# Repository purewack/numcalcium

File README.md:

# NumCalcium

NumCalcium is a calculator-like USB + Bluetooth Numpad keyboard. This is the primary intended function, however, because it is powered by MicroPython, users are able to write their own programs for it.
There were a number of different hardware and software revision before I settled on a combination of an ESP32 S3 and MicroPython. It made so much sense for the applications that I wanted to achieve, and was far easier to get working than my previous attempts with STM32F103 and a custom system in C, more about the development history below if you're interested :)

## Installation

You can download the release binary and flash it using esptool.py or other compatible ESP32 flashing tools.
You can also build the sources and / or change any config here to suit your needs, then flash the resulting binary.

The recommended method is to use the Makefile in this repo, which in turn uses `Docker` to pull the specific `esp-idf` version to build `MicroPython` against.

Hold down the encoder button (ESP32 GP0 pin) and reset the device, then:

```bash
make gen-ulp all deploy
```

## Hardware

The hardware contains an ESP32 S3 module with integrated PSRAM, a color LCD (320*170 px, ST7789), a rotary encoder, 20 mechanical switch buttons, SD card slot, USB (2.0) C port, Headphone jack, a buzzer, and exposed GPIO using an IDC connector.

### Pinout
The IDC connector can be used to plug in external hardware in three ways:
- using jumper wires onto a breadboard
- using a dedicated IDC cable 
- using the port to plug in custom PCBs

The last option is encouraged to develop standalone daughter boards with your custom hardware, including driver code, which can be stored on a flash chip located on the daughter board, and have NumCalcium read it and execute the code!

```
BACK VIEW - TOP

                TOP OF IDC CONNECTOR
[GND,   VBAT,   SDA/TX1, SCL/RX1, TX0,  RX0, GND, VCC]
[GP8,   GP7,    GP6,     GP5,     GP4,  GP3, GP2, GP1]

BACK VIEW - BOTTOM OF BOARD
```

The rotary encoder button is connected to GP0, which allows entering flash mode for firmware updates. The button is also monitored and treated separately from the keys as this button is intended to return to the main app switcher, [described in detail on its own repo.](https://github.com/purewack/numcalcium-apps.git)

The device has a built in li-ion battery charger and voltage regulator, so you can power the whole unit off a 18650 cell, and charge it while using it. The regulator + charger combo has been configured in such a way to provide enough current for charging and system demands.

There is an additional low power regulator designed to be always on, to keep the ESP32 powered during deep-sleep. The ESP32 can control the main regulator and turn it off to power down all other components on the board, except itself. By doing this, the board can have peripherals plugged in to the IDC port, but they will not drain the battery, as the regulator will disable VCC and another transistor will cut VBAT to the IDC port, which normally would be connected directly to the 18650 cell.

<ins>**Warning:**</ins>

The VBAT, as mentioned above, is connected to the positive terminal of the 18650 battery cell through a MOSFET, no other protection is provided from shorting the pin to ground, so caution must be taken as these cells can discharge a lot of current at once very quickly, most likely damaging the transistor before any real harm is done elsewhere, regardless caution is to be taken when operating near this pin!

The headphone jack is connected to the ESP32 via stereo RC filters, for crude PDM audio, which is experimental as the performance hit of the MicroPython interpreter has an impact on the scheduling of audio buffers at the time of writing.

The buzzer is a piezo element which can be used for 'beeps and boops' for feedback purposes when writing your own apps. Its also quite good at playing chiptunes ;)

The SD card slot and LCD screen are on the same SPI bus so it is advised to write code around this limitation in mind, avoiding using threads to address the screen and card at the same time to avoid data corruption and unwanted side effects.

The LCD is connected to SPI3 Bus, leaving SPI2 available to users on the IDC port.

The IDC port exposes two UART pairs, and I2C pins on the same pins which are used by 'cartridge' PCB featuring flash chips with driver code, allowing the board to setup the pins and further communication as needed.
The RX0 TX0 pair is permanently mapped to output `stdout` for developing applications which use USB, allowing users to still see debugging output on their console using UART converters.

There are addressable LEDs under each key and on the front next to the LCD. with give more options for UI UX design by for example highlighting keys that do something in a certain mode.

## Software

The main module which bundles all new and useful functionality compared to base MicroPython is `numcalc`.

This module contains classes making setting up common operations and pin assignments easier, specifically:
- interacting with the LCD
- LCD backlight adjustment
- a class specifically configuring the SD card slot
- buzzer tone control, 
- keypad input reading
- encoder turns and clicks
- LED control by obfuscating the neopixel class setup
- cartridge code loading and burning
- headphone PDM buffered audio streaming
- lcd BMP image parsing, framebuffer ready

> [class LCD() docs](docs/lcd.md)

> [class Keys() docs](docs/keys.md)

> [other `numcalc` functions docs](docs/other.md)

## Build and development

- Build and flash main firmware:

        make all
        make deploy

- Build and flash firmware with no modules, just c drivers:

        make firmware-no-freeze
        make deploy-no-freeze

- Build ULP code:

        make gen-ulp

- Build font file:
        make gen-font

- Update pin definitions:
        make gen-pins

# Devlog

I have included a development history going back through different [hardware designs and software paradigms.](devlog/HISTORY.md)

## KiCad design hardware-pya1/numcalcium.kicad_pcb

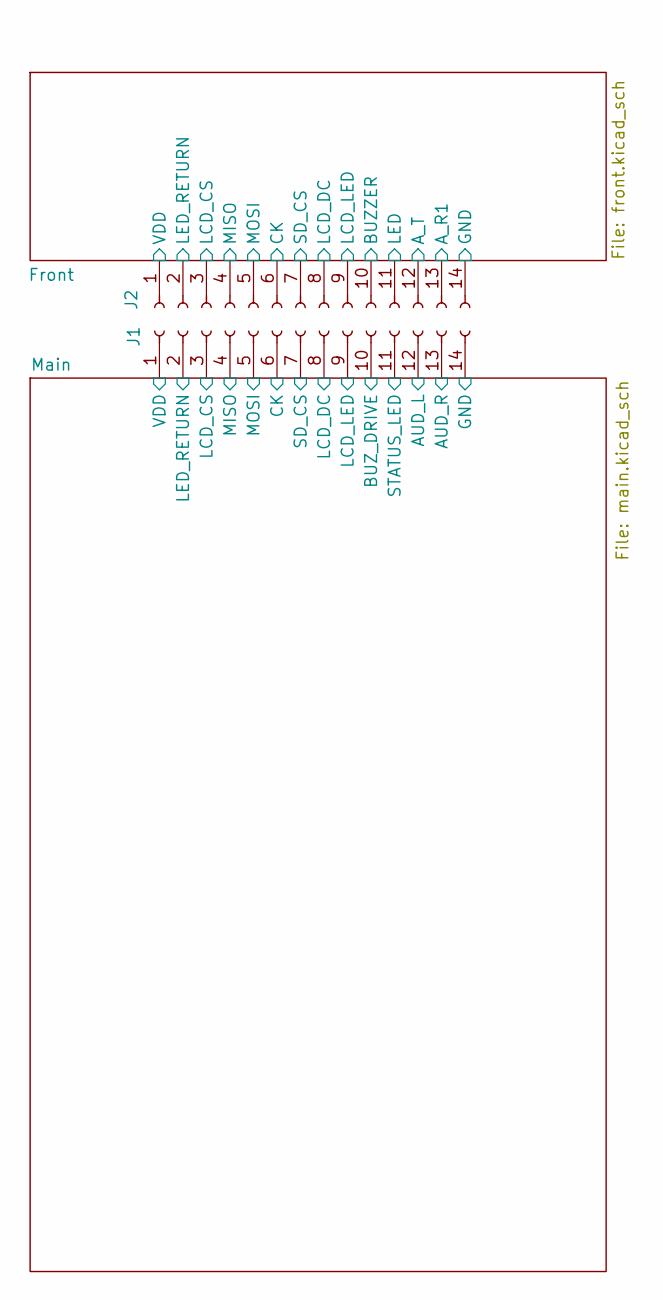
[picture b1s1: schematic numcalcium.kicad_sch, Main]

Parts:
J1, J2: Conn_01x14_Socket; Hirose_FH12-14S-0.5SH_1x14-1MP_P0.50mm_Horizontal

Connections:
/Front/A_R1: J2.13; also elsewhere on the board
/Front/A_T: J2.12; also elsewhere on the board
/Front/BUZZER: J2.10; also elsewhere on the board
/Front/CK: J2.6; also elsewhere on the board
/Front/GND: J2.14; also elsewhere on the board
/Front/LCD_CS: J2.3; also elsewhere on the board
/Front/LCD_DC: J2.8; also elsewhere on the board
/Front/LCD_LED: J2.9; also elsewhere on the board
/Front/LED: J2.11; also elsewhere on the board
/Front/LED_RETURN: J2.2; also elsewhere on the board
/Front/MISO: J2.4; also elsewhere on the board
/Front/MOSI: J2.5; also elsewhere on the board
/Front/SD_CS: J2.7; also elsewhere on the board
/Front/VDD: J2.1; also elsewhere on the board
/Main/AUD_L: J1.12; also elsewhere on the board
/Main/AUD_R: J1.13; also elsewhere on the board
/Main/BUZ_DRIVE: J1.10; also elsewhere on the board
/Main/CK: J1.6; also elsewhere on the board
/Main/LCD_CS: J1.3; also elsewhere on the board
/Main/LCD_DC: J1.8; also elsewhere on the board
/Main/LCD_LED: J1.9; also elsewhere on the board
/Main/LED_RETURN: J1.2; also elsewhere on the board
/Main/MISO: J1.4; also elsewhere on the board
/Main/MOSI: J1.5; also elsewhere on the board
/Main/SD_CS: J1.7; also elsewhere on the board
/Main/STATUS_LED: J1.11; also elsewhere on the board
GND: J1.14; also elsewhere on the board
VDD: J1.1; also elsewhere on the board

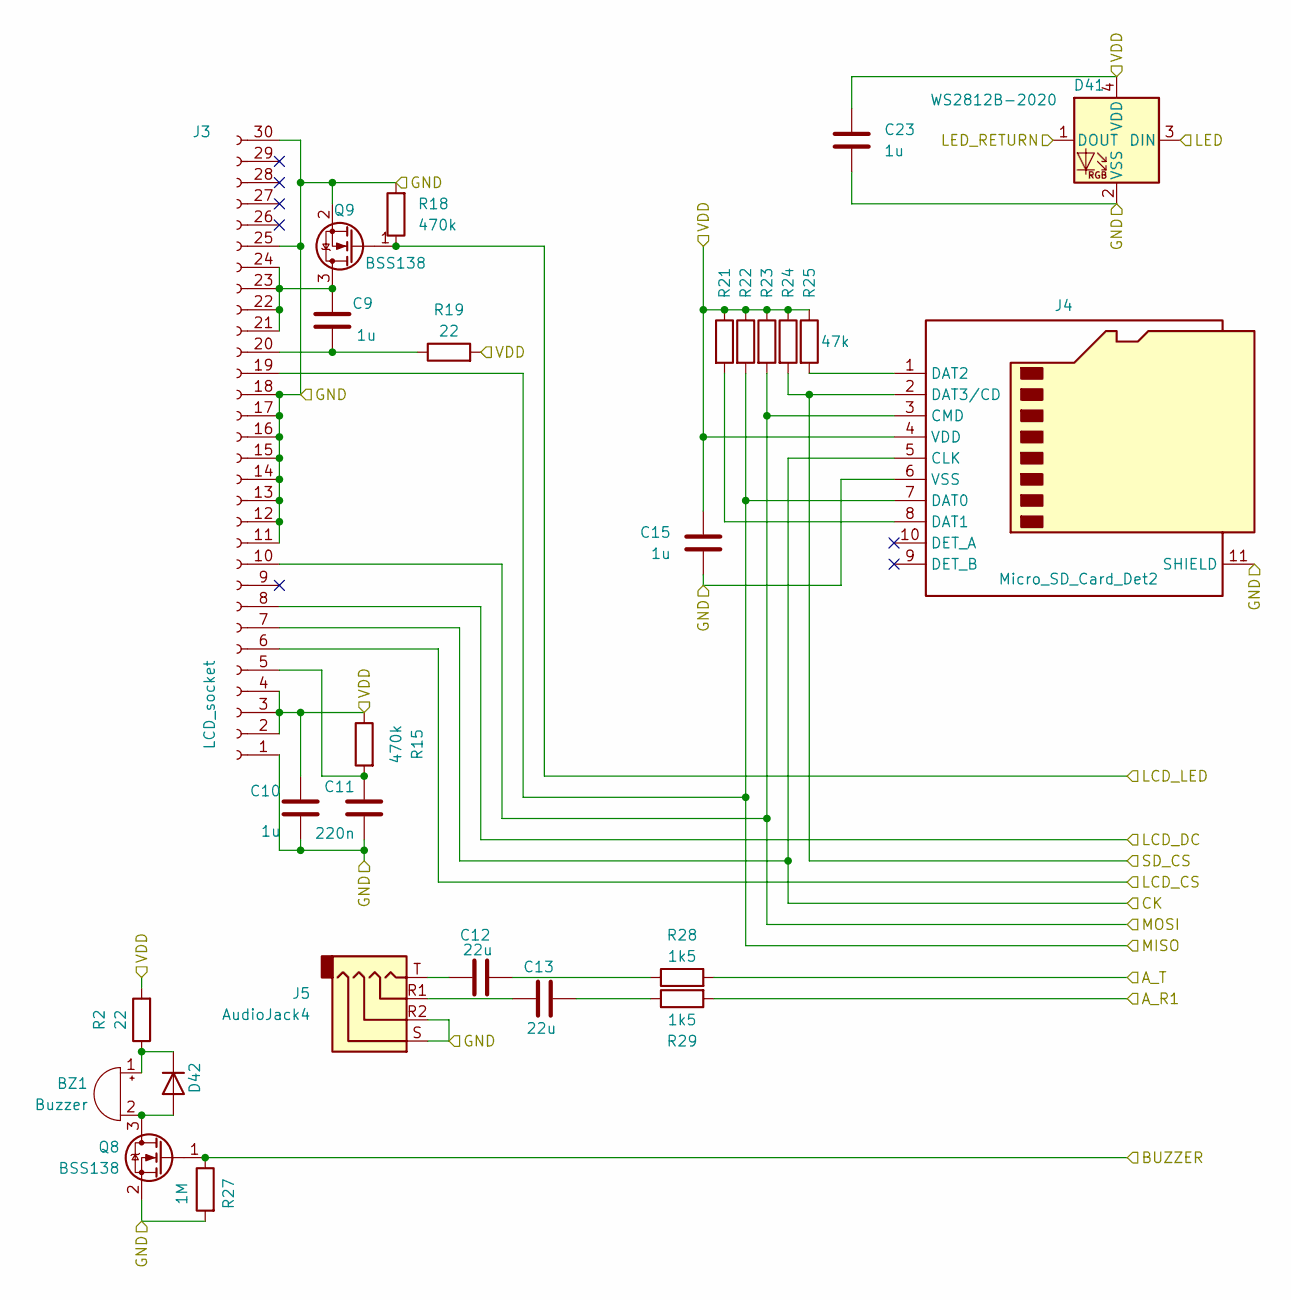
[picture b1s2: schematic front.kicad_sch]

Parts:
BZ1: Buzzer; MagneticBuzzer_CUI_CMT-8504-100-SMT
C9, C10, C15, C23: 1u; C_0805_2012Metric_Pad1.18x1.45mm_HandSolder
C11: 220n; C_0805_2012Metric_Pad1.18x1.45mm_HandSolder
C12, C13: 22u; C_1206_3216Metric_Pad1.33x1.80mm_HandSolder
D41: WS2812B-2020; LED_WS2812B-2020_PLCC4_2.0x2.0mm
D42: 1N4148; D_1206_3216Metric
J3: LCD_socket; Hirose_FH12-30S-0.5SH_1x30-1MP_P0.50mm_Horizontal
J4: Micro_SD_Card_Det2; microSD_Short_1
J5: AudioJack4; Jack_3.5mm_PJ320D_Horizontal
Q8, Q9: BSS138; SOT-23
R2, R19: 22; R_0805_2012Metric_Pad1.20x1.40mm_HandSolder
R15, R18: 470k; R_0805_2012Metric_Pad1.20x1.40mm_HandSolder
R21, R22, R23, R24, R25: 47k; R_0805_2012Metric_Pad1.20x1.40mm_HandSolder
R27: 1M; R_0805_2012Metric_Pad1.20x1.40mm_HandSolder
R28, R29: 1k5; R_0805_2012Metric_Pad1.20x1.40mm_HandSolder

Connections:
/Front/A_R1: R29.2; also elsewhere on the board
/Front/A_T: R28.2; also elsewhere on the board
/Front/BUZZER: Q8.1 (G), R27.1; also elsewhere on the board
/Front/CK: J3.7, J4.5 (CLK); also elsewhere on the board
/Front/GND: C10.2, C11.2, C15.2, C23.2, D41.2 (VSS), J3.1, J3.11, J3.12, J3.13, J3.14, J3.15, J3.16, J3.17, J3.18, J3.25, J3.30, J4.6 (VSS), J4.11 (SHIELD), J5.R2, J5.S, Q8.2 (S), Q9.2 (S), R18.2, R27.2; also elsewhere on the board
/Front/LCD_CS: J3.6; also elsewhere on the board
/Front/LCD_DC: J3.8; also elsewhere on the board
/Front/LCD_LED: Q9.1 (G), R18.1; also elsewhere on the board
/Front/LED: D41.3 (DIN); also elsewhere on the board
/Front/LED_RETURN: D41.1 (DOUT); also elsewhere on the board
/Front/MISO: J3.19, J4.7 (DAT0), R22.2; also elsewhere on the board
/Front/MOSI: J3.10, J4.3 (CMD), R23.2; also elsewhere on the board
/Front/SD_CS: J4.2 (DAT3/CD), R24.2; also elsewhere on the board
/Front/VDD: C10.1, C15.1, C23.1, D41.4 (VDD), J3.2, J3.3, J3.4, J4.4 (VDD), R2.2, R15.1, R19.2, R21.1, R22.1, R23.1, R24.1, R25.1; also elsewhere on the board
unnamed: BZ1.1 (+), D42.1 (K), R2.1
unnamed: BZ1.2 (-), D42.2 (A), Q8.3 (D)
unnamed: C12.1, J5.T
unnamed: C12.2, R28.1
unnamed: C13.1, J5.R1
unnamed: C13.2, R29.1
unnamed: C11.1, J3.5, R15.2
unnamed: C9.2, J3.20, R19.1
unnamed: C9.1, J3.21, J3.22, J3.23, J3.24, Q9.3 (D)
unnamed: J4.8 (DAT1), R21.2
unnamed: J4.1 (DAT2), R25.2

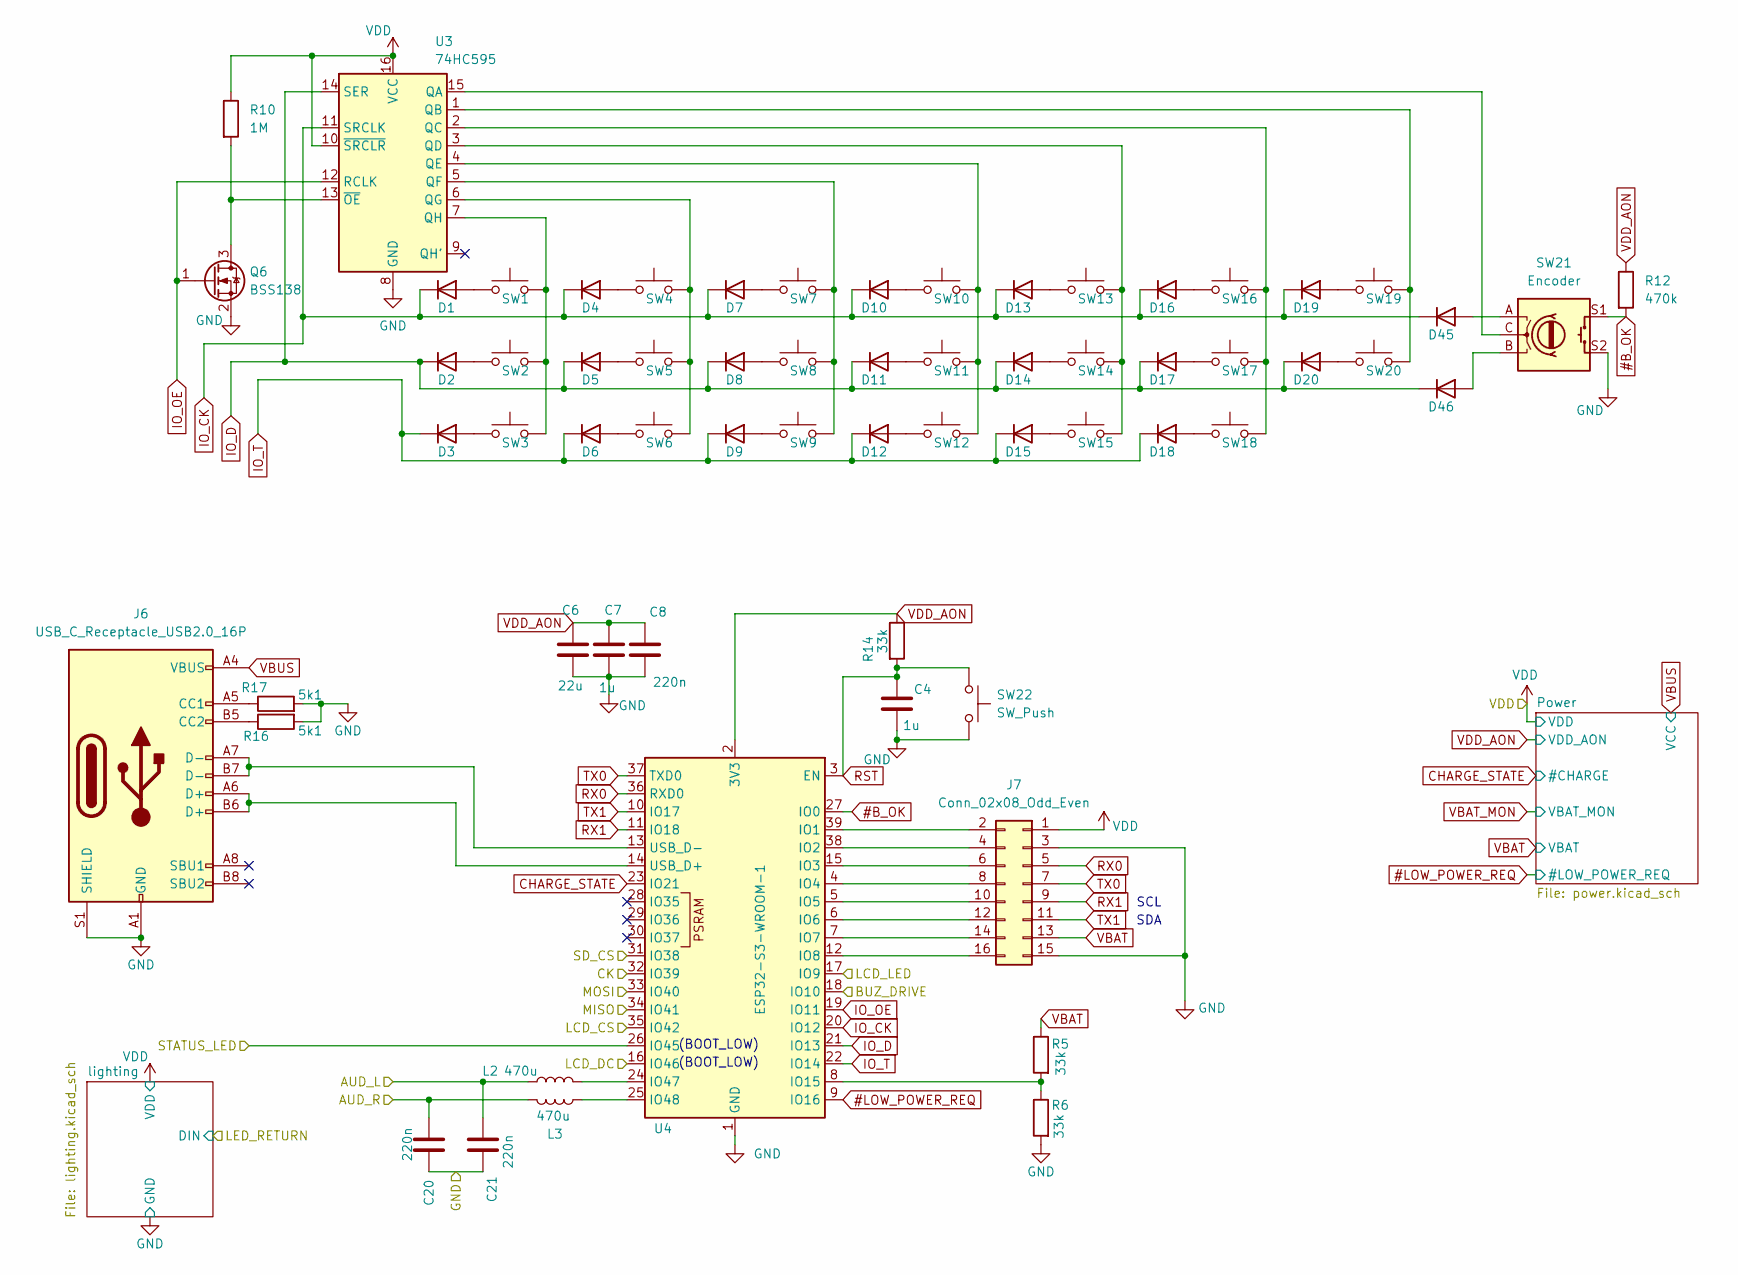
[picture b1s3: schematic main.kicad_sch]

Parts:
C4, C7: 1u; C_0805_2012Metric_Pad1.18x1.45mm_HandSolder
C6: 22u; C_1206_3216Metric_Pad1.33x1.80mm_HandSolder
C8, C20, C21: 220n; C_0805_2012Metric_Pad1.18x1.45mm_HandSolder
D1, D2, D3, D4, D5, D6, D7, D8, D9, D10, D11, D12, D13, D14, D15, D16, D17, D18, D19, D20, D45, D46: 1N4148; D_1206_3216Metric
J6: USB_C_Receptacle_USB2.0_16P; USB_C_Receptacle_GCT_USB4105-xx-A_16P_TopMnt_Horizontal
J7: Conn_02x08_Odd_Even; IDC-Header_2x08_P2.54mm_Horizontal
L2, L3: 470u; L_1210_3225Metric
Q6: BSS138; SOT-23
R5, R6, R14: 33k; R_0805_2012Metric_Pad1.20x1.40mm_HandSolder
R10: 1M; R_0805_2012Metric_Pad1.20x1.40mm_HandSolder
R12: 470k; R_0805_2012Metric_Pad1.20x1.40mm_HandSolder
R16, R17: 5k1; R_0805_2012Metric_Pad1.20x1.40mm_HandSolder
SW1, SW2, SW3, SW4, SW5, SW6, SW7, SW8, SW9, SW10, SW11, SW12, SW13, SW14, SW15, SW16, SW17, SW18, SW19, SW20: SW_Push; SW_Cherry_MX_1.00u_PCB
SW21: Encoder; RotaryEncoder_Alps_EC11E-Switch_Vertical_H20mm
SW22: SW_Push; SW_SPST_PTS647_Sx38
U3: 74HC595; TSSOP-16_4.4x5mm_P0.65mm
U4: ESP32-S3-WROOM-1; ESP32-S3-WROOM-1-Compact-Court

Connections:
#B_OK: R12.2, SW21.S1, U4.27 (IO0)
#LOW_POWER_REQ: U4.9 (IO16); also elsewhere on the board
/Main/AUD_L: C21.2, L2.1; also elsewhere on the board
/Main/AUD_R: C20.2, L3.2; also elsewhere on the board
/Main/BUZ_DRIVE: U4.18 (IO10); also elsewhere on the board
/Main/CK: U4.32 (IO39); also elsewhere on the board
/Main/LCD_CS: U4.35 (IO42); also elsewhere on the board
/Main/LCD_DC: U4.16 (IO46); also elsewhere on the board
/Main/LCD_LED: U4.17 (IO9); also elsewhere on the board
/Main/MISO: U4.34 (IO41); also elsewhere on the board
/Main/MOSI: U4.33 (IO40); also elsewhere on the board
/Main/SD_CS: U4.31 (IO38); also elsewhere on the board
/Main/STATUS_LED: U4.26 (IO45); also elsewhere on the board
CHARGE_STATE: U4.23 (IO21); also elsewhere on the board
GND: C4.2, C6.2, C7.2, C8.2, C20.1, C21.1, J6.A1 (GND), J6.A12 (GND), J6.B1 (GND), J6.B12 (GND), J6.S1 (SHIELD), J7.3, J7.15, Q6.2 (S), R6.2, R16.2, R17.2, SW21.S2, SW22.2, U3.8 (GND), U4.1 (GND), U4.40 (GND), U4.41 (GND); also elsewhere on the board
IO_CK: D1.1 (K), D4.1 (K), D7.1 (K), D10.1 (K), D13.1 (K), D16.1 (K), D19.1 (K), D45.1 (K), U3.11 (SRCLK), U4.20 (IO12)
IO_D: D2.1 (K), D5.1 (K), D8.1 (K), D11.1 (K), D14.1 (K), D17.1 (K), D20.1 (K), D46.1 (K), U3.14 (SER), U4.21 (IO13)
IO_OE: Q6.1 (G), U3.12 (RCLK), U4.19 (IO11)
IO_T: D3.1 (K), D6.1 (K), D9.1 (K), D12.1 (K), D15.1 (K), D18.1 (K), U4.22 (IO14)
unnamed: D1.2 (A), SW1.2
unnamed: D2.2 (A), SW2.2
unnamed: D3.2 (A), SW3.2
unnamed: D4.2 (A), SW4.2
unnamed: D5.2 (A), SW5.2
unnamed: D6.2 (A), SW6.2
unnamed: D7.2 (A), SW7.2
unnamed: D8.2 (A), SW8.2
unnamed: D9.2 (A), SW9.2
unnamed: D10.2 (A), SW10.2
unnamed: D11.2 (A), SW11.2
unnamed: D12.2 (A), SW12.2
unnamed: D13.2 (A), SW13.2
unnamed: D14.2 (A), SW14.2
unnamed: D15.2 (A), SW15.2
unnamed: D16.2 (A), SW16.2
unnamed: D17.2 (A), SW17.2
unnamed: D18.2 (A), SW18.2
unnamed: D19.2 (A), SW19.2
unnamed: D20.2 (A), SW20.2
unnamed: D45.2 (A), SW21.A
unnamed: D46.2 (A), SW21.B
unnamed: J6.A5 (CC1), R17.1
unnamed: J6.B5 (CC2), R16.1
unnamed: J7.2, U4.39 (IO1)
unnamed: J7.4, U4.38 (IO2)
unnamed: J7.6, U4.15 (IO3)
unnamed: J7.8, U4.4 (IO4)
unnamed: J7.10, U4.5 (IO5)
unnamed: J7.12, U4.6 (IO6)
unnamed: J7.14, U4.7 (IO7)
unnamed: J7.16, U4.12 (IO8)
unnamed: Q6.3 (D), R10.2, U3.13 (~OE)
unnamed: SW21.C, U3.15 (QA)
unnamed: SW19.1, SW20.1, U3.1 (QB)
unnamed: SW16.1, SW17.1, SW18.1, U3.2 (QC)
unnamed: SW13.1, SW14.1, SW15.1, U3.3 (QD)
unnamed: SW10.1, SW11.1, SW12.1, U3.4 (QE)
unnamed: SW7.1, SW8.1, SW9.1, U3.5 (QF)
unnamed: SW4.1, SW5.1, SW6.1, U3.6 (QG)
unnamed: SW1.1, SW2.1, SW3.1, U3.7 (QH)
unnamed: R5.2, R6.1, U4.8 (IO15)
unnamed: L2.2, U4.24 (IO47)
unnamed: L3.1, U4.25 (IO48)
unnamed: J6.A6 (D+), J6.B6 (D+), U4.14 (USB_D+)
unnamed: J6.A7 (D-), J6.B7 (D-), U4.13 (USB_D-)
RST: C4.1, R14.2, SW22.1, U4.3 (EN)
RX0: J7.5, U4.36 (RXD0)
RX1: J7.9, U4.11 (IO18)
TX0: J7.7, U4.37 (TXD0)
TX1: J7.11, U4.10 (IO17)
VBAT: J7.13, R5.1; also elsewhere on the board
VBUS: J6.A4 (VBUS), J6.A9 (VBUS), J6.B4 (VBUS), J6.B9 (VBUS); also elsewhere on the board
VDD: J7.1, R10.1, U3.10 (~SRCLR), U3.16 (VCC); also elsewhere on the board
VDD_AON: C6.1, C7.1, C8.1, R12.1, R14.1, U4.2 (3V3); also elsewhere on the board

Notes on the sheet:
SCL
(BOOT_LOW)
SDA

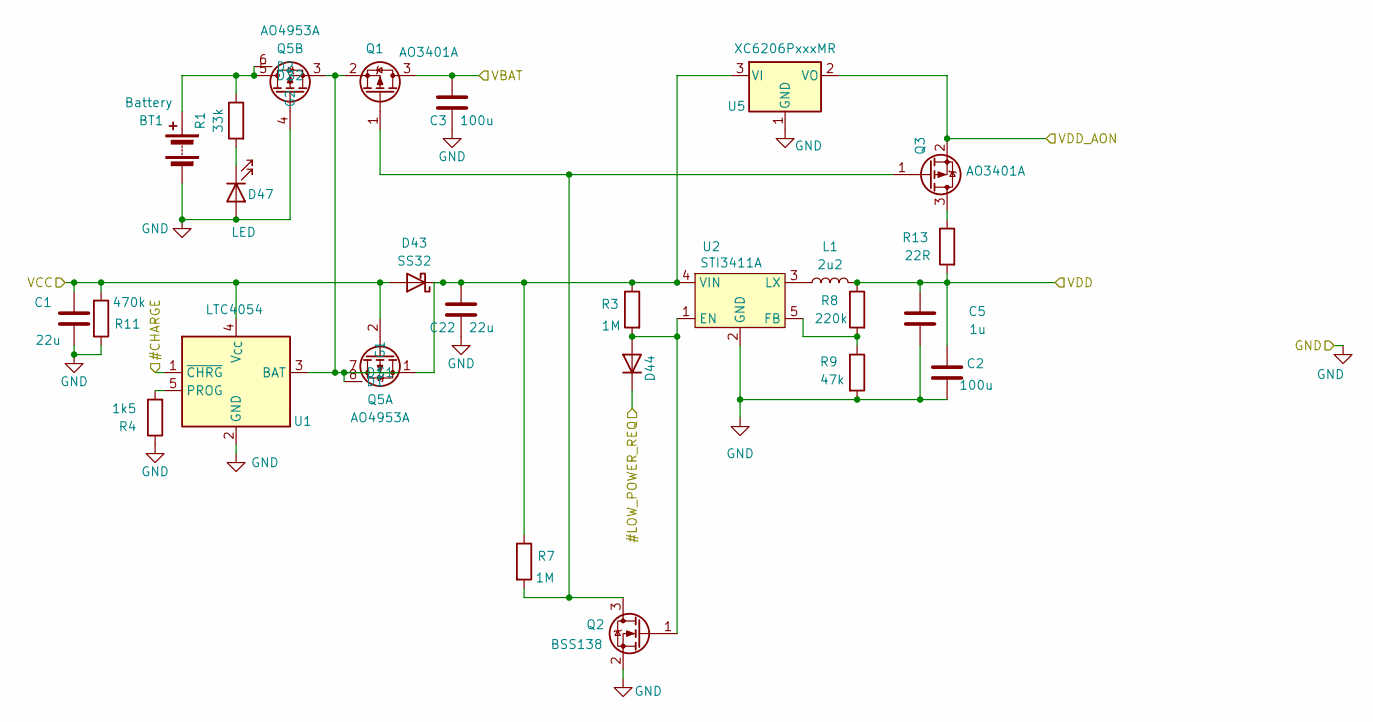
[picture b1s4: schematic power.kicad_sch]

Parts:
BT1: Battery; LiIon18650
C1, C22: 22u; C_1206_3216Metric_Pad1.33x1.80mm_HandSolder
C2, C3: 100u; CP_EIA-7343-31_Kemet-D
C5: 1u; C_0805_2012Metric_Pad1.18x1.45mm_HandSolder
D43: SS32; D_SMA
D44: 1N4148; D_1206_3216Metric
D47: LED; D_1206_3216Metric
L1: 2u2; L_Chilisin_BMRA00050530
Q1, Q3: AO3401A; SOT-23
Q2: BSS138; SOT-23
Q5: AO4953A; SOP-8_3.9x4.9mm_P1.27mm
R1: 33k; R_0805_2012Metric_Pad1.20x1.40mm_HandSolder
R3, R7: 1M; R_0805_2012Metric_Pad1.20x1.40mm_HandSolder
R4: 1k5; R_0805_2012Metric_Pad1.20x1.40mm_HandSolder
R8: 220k; R_0805_2012Metric_Pad1.20x1.40mm_HandSolder
R9: 47k; R_0805_2012Metric_Pad1.20x1.40mm_HandSolder
R11: 470k; R_0805_2012Metric_Pad1.20x1.40mm_HandSolder
R13: 22R; R_0805_2012Metric_Pad1.20x1.40mm_HandSolder
U1: LTC4054; TSOT-23-5
U2: STI3411A; TSOT-23-5
U5: XC6206PxxxMR; SOT-23-3

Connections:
#LOW_POWER_REQ: D44.1 (K); also elsewhere on the board
CHARGE_STATE: U1.1 (~CHRG); also elsewhere on the board
GND: BT1.2 (-), C1.2, C2.2, C3.2, C5.2, C22.2, D47.2 (A), Q2.2 (S), Q5.4 (G2), R4.1, R9.2, R11.1, U1.2 (GND), U2.2 (GND), U5.1 (GND); also elsewhere on the board
unnamed: BT1.1 (+), Q5.5 (D2), Q5.6 (D2), R1.1
unnamed: C22.1, D43.1 (K), Q5.1 (S1), R3.1, R7.1, U2.4 (VIN), U5.3 (VI)
unnamed: D44.2 (A), Q2.1 (G), R3.2, U2.1 (EN)
unnamed: D47.1 (K), R1.2
unnamed: Q1.1 (G), Q2.3 (D), Q3.1 (G), R7.2
unnamed: Q1.2 (S), Q5.3 (S2), Q5.7 (D1), Q5.8 (D1), U1.3 (BAT)
unnamed: Q3.3 (D), R13.1
unnamed: R4.2, U1.5 (PROG)
unnamed: R8.2, R9.1, U2.5 (FB)
unnamed: L1.1, U2.3 (LX)
VBAT: C3.1, Q1.3 (D); also elsewhere on the board
VBUS: C1.1, D43.2 (A), Q5.2 (G1), R11.2, U1.4 (V_{CC}); also elsewhere on the board
VDD: C2.1, C5.1, L1.2, R8.1, R13.2; also elsewhere on the board
VDD_AON: Q3.2 (S), U5.2 (VO); also elsewhere on the board

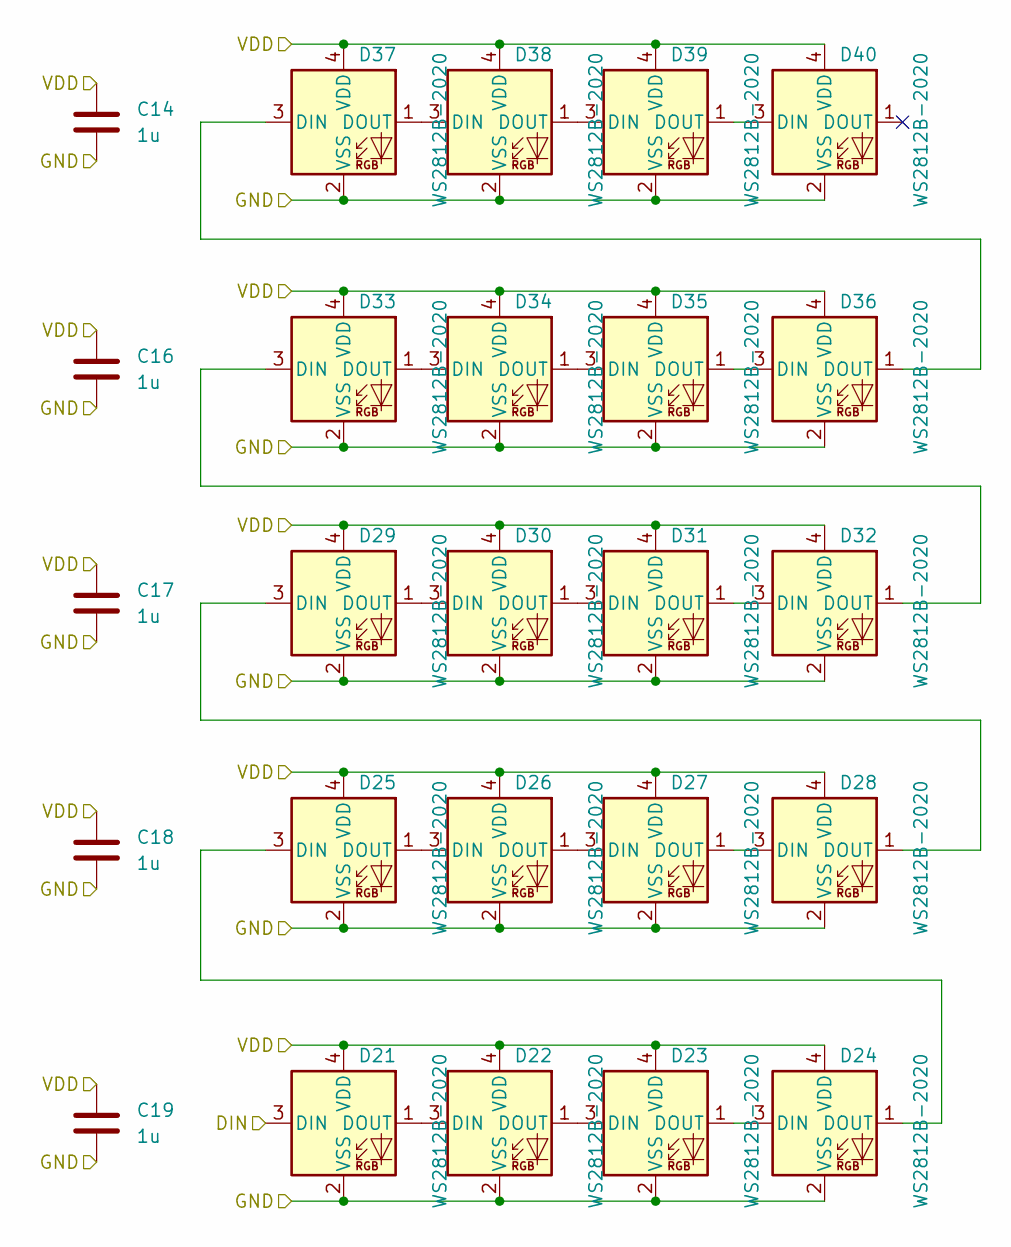
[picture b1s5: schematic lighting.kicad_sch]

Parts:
C14, C16, C17, C18, C19: 1u; C_0805_2012Metric_Pad1.18x1.45mm_HandSolder
D21, D22, D23, D24, D25, D26, D27, D28, D29, D30, D31, D32, D33, D34, D35, D36, D37, D38, D39, D40: WS2812B-2020; LED_WS2812B-2020_PLCC4_2.0x2.0mm

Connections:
/Main/LED_RETURN: D21.3 (DIN); also elsewhere on the board
GND: C14.2, C16.2, C17.2, C18.2, C19.2, D21.2 (VSS), D22.2 (VSS), D23.2 (VSS), D24.2 (VSS), D25.2 (VSS), D26.2 (VSS), D27.2 (VSS), D28.2 (VSS), D29.2 (VSS), D30.2 (VSS), D31.2 (VSS), D32.2 (VSS), D33.2 (VSS), D34.2 (VSS), D35.2 (VSS), D36.2 (VSS), D37.2 (VSS), D38.2 (VSS), D39.2 (VSS), D40.2 (VSS); also elsewhere on the board
unnamed: D21.1 (DOUT), D22.3 (DIN)
unnamed: D22.1 (DOUT), D23.3 (DIN)
unnamed: D23.1 (DOUT), D24.3 (DIN)
unnamed: D24.1 (DOUT), D25.3 (DIN)
unnamed: D25.1 (DOUT), D26.3 (DIN)
unnamed: D26.1 (DOUT), D27.3 (DIN)
unnamed: D27.1 (DOUT), D28.3 (DIN)
unnamed: D28.1 (DOUT), D29.3 (DIN)
unnamed: D29.1 (DOUT), D30.3 (DIN)
unnamed: D30.1 (DOUT), D31.3 (DIN)
unnamed: D31.1 (DOUT), D32.3 (DIN)
unnamed: D32.1 (DOUT), D33.3 (DIN)
unnamed: D33.1 (DOUT), D34.3 (DIN)
unnamed: D34.1 (DOUT), D35.3 (DIN)
unnamed: D35.1 (DOUT), D36.3 (DIN)
unnamed: D36.1 (DOUT), D37.3 (DIN)
unnamed: D37.1 (DOUT), D38.3 (DIN)
unnamed: D38.1 (DOUT), D39.3 (DIN)
unnamed: D39.1 (DOUT), D40.3 (DIN)
VDD: C14.1, C16.1, C17.1, C18.1, C19.1, D21.4 (VDD), D22.4 (VDD), D23.4 (VDD), D24.4 (VDD), D25.4 (VDD), D26.4 (VDD), D27.4 (VDD), D28.4 (VDD), D29.4 (VDD), D30.4 (VDD), D31.4 (VDD), D32.4 (VDD), D33.4 (VDD), D34.4 (VDD), D35.4 (VDD), D36.4 (VDD), D37.4 (VDD), D38.4 (VDD), D39.4 (VDD), D40.4 (VDD); also elsewhere on the board

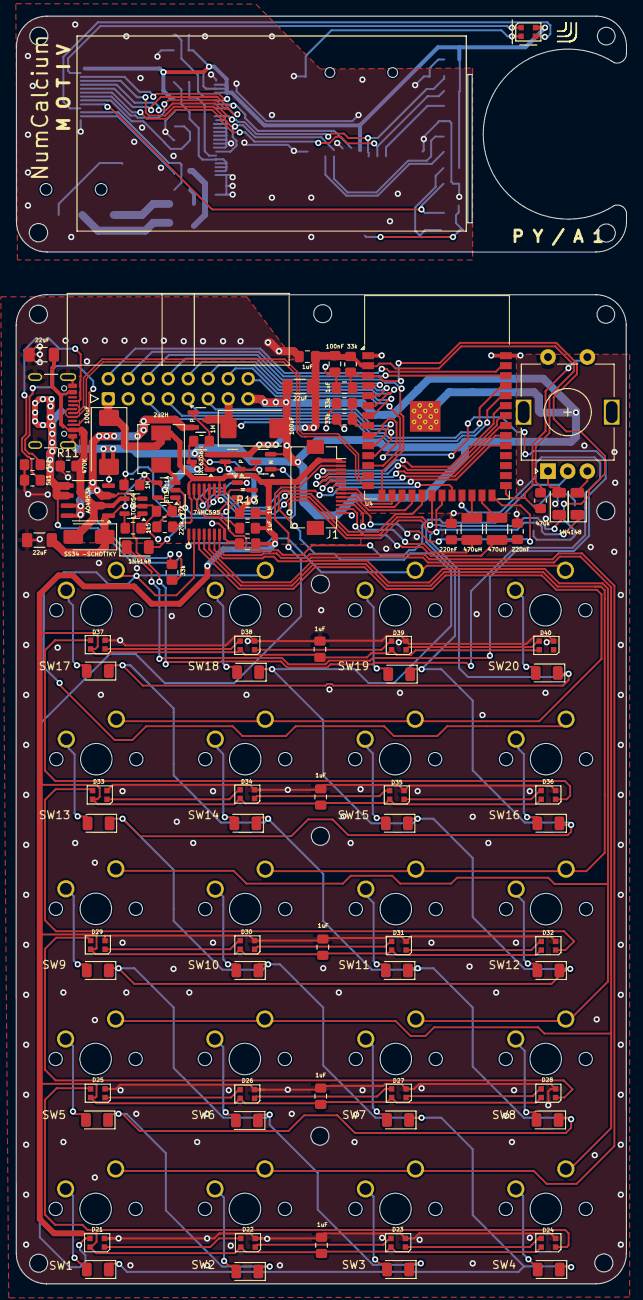
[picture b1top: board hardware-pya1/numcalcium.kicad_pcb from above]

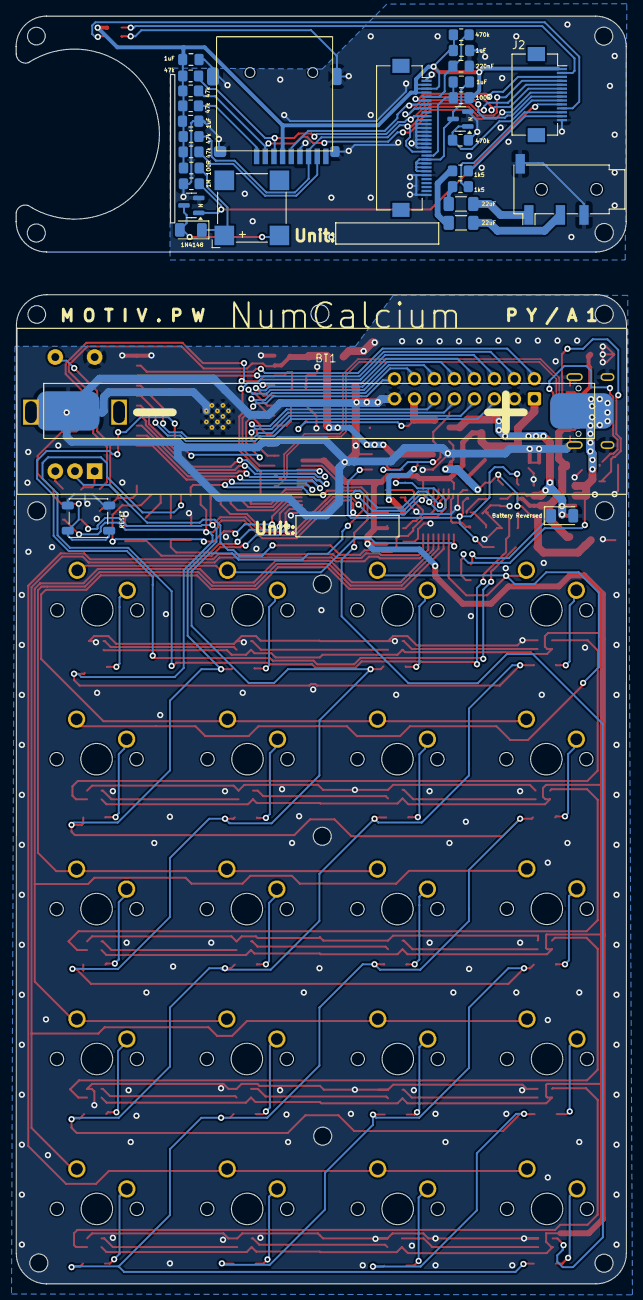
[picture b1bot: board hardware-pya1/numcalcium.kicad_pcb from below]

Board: 2 copper layers, 77.5 x 125.7 mm, 143 parts (30 on the bottom side), 129 nets.

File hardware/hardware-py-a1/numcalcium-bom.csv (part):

"Reference","Value","Footprint"
"BT1","Battery","footprints:LiIon18650"
"BZ1","Buzzer","Buzzer_Beeper:MagneticBuzzer_CUI_CMT-8504-100-SMT"
"C1","100uF","Capacitor_SMD:C_1210_3225Metric"
"C2","220u","Capacitor_SMD:C_2220_5750Metric"
"C3","47u","Capacitor_SMD:C_1210_3225Metric_Pad1.33x2.70mm_HandSolder"
"C4","1u","Capacitor_SMD:C_0805_2012Metric"
"C5","22u","Capacitor_SMD:C_1210_3225Metric"
"C6","220u","Capacitor_SMD:C_2220_5750Metric"
"C7","1u","Capacitor_SMD:C_1206_3216Metric"
"C8","100n","Capacitor_SMD:C_0805_2012Metric"
"C9","1u","Capacitor_SMD:C_0805_2012Metric"
"C10","1u","Capacitor_SMD:C_0805_2012Metric"
"C11","100n","Capacitor_SMD:C_0805_2012Metric"
"C12","22u","Capacitor_SMD:C_1210_3225Metric"
"C13","22u","Capacitor_SMD:C_1210_3225Metric"
"C14","1u","Capacitor_SMD:C_0805_2012Metric_Pad1.18x1.45mm_HandSolder"
"C15","10u","Capacitor_SMD:C_0805_2012Metric"
"C16","1u","Capacitor_SMD:C_0805_2012Metric_Pad1.18x1.45mm_HandSolder"
"C17","1u","Capacitor_SMD:C_0805_2012Metric_Pad1.18x1.45mm_HandSolder"
"C18","1u","Capacitor_SMD:C_0805_2012Metric_Pad1.18x1.45mm_HandSolder"
"C19","1u","Capacitor_SMD:C_0805_2012Metric_Pad1.18x1.45mm_HandSolder"
"C20","220n","Capacitor_SMD:C_0805_2012Metric"
"C21","220n","Capacitor_SMD:C_0805_2012Metric"
"C22","100u","Capacitor_SMD:C_1210_3225Metric_Pad1.33x2.70mm_HandSolder"
"C23","2u2","Capacitor_SMD:C_0805_2012Metric"
"D1","D","Diode_SMD:D_1206_3216Metric"
"D2","D","Diode_SMD:D_1206_3216Metric"
"D3","D","Diode_SMD:D_1206_3216Metric"
"D4","D","Diode_SMD:D_1206_3216Metric"
"D5","D","Diode_SMD:D_1206_3216Metric"
"D6","D","Diode_SMD:D_1206_3216Metric"
"D7","D","Diode_SMD:D_1206_3216Metric"
"D8","D","Diode_SMD:D_1206_3216Metric"
"D9","D","Diode_SMD:D_1206_3216Metric"
"D10","D","Diode_SMD:D_1206_3216Metric"
"D11","D","Diode_SMD:D_1206_3216Metric"
"D12","D","Diode_SMD:D_1206_3216Metric"
"D13","D","Diode_SMD:D_1206_3216Metric"
"D14","D","Diode_SMD:D_1206_3216Metric"
"D15","D","Diode_SMD:D_1206_3216Metric"
"D16","D","Diode_SMD:D_1206_3216Metric"
"D17","D","Diode_SMD:D_1206_3216Metric"
"D18","D","Diode_SMD:D_1206_3216Metric"
"D19","D","Diode_SMD:D_1206_3216Metric"
"D20","D","Diode_SMD:D_1206_3216Metric"
"D21","WS2812B-2020","LED_SMD:LED_WS2812B-2020_PLCC4_2.0x2.0mm"
"D22","WS2812B-2020","LED_SMD:LED_WS2812B-2020_PLCC4_2.0x2.0mm"
"D23","WS2812B-2020","LED_SMD:LED_WS2812B-2020_PLCC4_2.0x2.0mm"
"D24","WS2812B-2020","LED_SMD:LED_WS2812B-2020_PLCC4_2.0x2.0mm"
"D25","WS2812B-2020","LED_SMD:LED_WS2812B-2020_PLCC4_2.0x2.0mm"
"D26","WS2812B-2020","LED_SMD:LED_WS2812B-2020_PLCC4_2.0x2.0mm"
"D27","WS2812B-2020","LED_SMD:LED_WS2812B-2020_PLCC4_2.0x2.0mm"
"D28","WS2812B-2020","LED_SMD:LED_WS2812B-2020_PLCC4_2.0x2.0mm"
"D29","WS2812B-2020","LED_SMD:LED_WS2812B-2020_PLCC4_2.0x2.0mm"
"D30","WS2812B-2020","LED_SMD:LED_WS2812B-2020_PLCC4_2.0x2.0mm"
"D31","WS2812B-2020","LED_SMD:LED_WS2812B-2020_PLCC4_2.0x2.0mm"
"D32","WS2812B-2020","LED_SMD:LED_WS2812B-2020_PLCC4_2.0x2.0mm"
"D33","WS2812B-2020","LED_SMD:LED_WS2812B-2020_PLCC4_2.0x2.0mm"
"D34","WS2812B-2020","LED_SMD:LED_WS2812B-2020_PLCC4_2.0x2.0mm"
"D35","WS2812B-2020","LED_SMD:LED_WS2812B-2020_PLCC4_2.0x2.0mm"
"D36","WS2812B-2020","LED_SMD:LED_WS2812B-2020_PLCC4_2.0x2.0mm"
"D37","WS2812B-2020","LED_SMD:LED_WS2812B-2020_PLCC4_2.0x2.0mm"
"D38","WS2812B-2020","LED_SMD:LED_WS2812B-2020_PLCC4_2.0x2.0mm"
"D39","WS2812B-2020","LED_SMD:LED_WS2812B-2020_PLCC4_2.0x2.0mm"
"D40","WS2812B-2020","LED_SMD:LED_WS2812B-2020_PLCC4_2.0x2.0mm"
"D41","WS2812B-2020","LED_SMD:LED_WS2812B-2020_PLCC4_2.0x2.0mm"
"D42","D","Diode_SMD:D_1206_3216Metric"
"D43","SS32","Diode_SMD:D_SMA"
"D44","D","Diode_SMD:D_1206_3216Metric"
"D45","D","Diode_SMD:D_1206_3216Metric"
"D46","D","Diode_SMD:D_1206_3216Metric"
"D47","BAT_REV","Diode_SMD:D_1206_3216Metric"
"J1","Conn_01x14_Socket","Connector_FFC-FPC:Hirose_FH12-14S-0.5SH_1x14-1MP_P0.50mm_Horizontal"
"J2","Conn_01x14_Socket","Connector_FFC-FPC:Hirose_FH12-14S-0.5SH_1x14-1MP_P0.50mm_Horizontal"
"J3","LCD_socket","Connector_FFC-FPC:Hirose_FH12-30S-0.5SH_1x30-1MP_P0.50mm_Horizontal"
"J4","Micro_SD_Card_Det2","footprints:microSD_Short_1"
"J5","AudioJack4","footprints:Jack_3.5mm_PJ320D_Horizontal"
"J6","USB_C_Receptacle_USB2.0_16P","Connector_USB:USB_C_Receptacle_GCT_USB4105-xx-A_16P_TopMnt_Horizontal"
"J7","Conn_02x08_Odd_Even","footprints:IDC-Header_2x08_P2.54mm_Horizontal"
"L1","2u2","Inductor_SMD:L_Chilisin_BMRA00050530"
"L2","470u","Inductor_SMD:L_1210_3225Metric"
"L3","470u","Inductor_SMD:L_1210_3225Metric"
"Q1","AO3401A","Package_TO_SOT_SMD:SOT-23"
"Q2","BSS138","Package_TO_SOT_SMD:SOT-23"
"Q3","AO3401A","Package_TO_SOT_SMD:SOT-23"
"Q5","AO4953A","Package_SO:SOP-8_3.9x4.9mm_P1.27mm"
"Q6","BSS138","Package_TO_SOT_SMD:SOT-23"
"Q8","BSS138","Package_TO_SOT_SMD:SOT-23"
"Q9","BSS138","Package_TO_SOT_SMD:SOT-23"
"R1","33k","Resistor_SMD:R_0805_2012Metric_Pad1.20x1.40mm_HandSolder"
"R2","47","Resistor_SMD:R_0805_2012Metric_Pad1.20x1.40mm_HandSolder"
"R3","1M","Resistor_SMD:R_0805_2012Metric_Pad1.20x1.40mm_HandSolder"
"R4","1k","Resistor_SMD:R_0805_2012Metric_Pad1.20x1.40mm_HandSolder"
"R5","33k","Resistor_SMD:R_0805_2012Metric_Pad1.20x1.40mm_HandSolder"
"R6","33k","Resistor_SMD:R_0805_2012Metric_Pad1.20x1.40mm_HandSolder"
"R7","1M","Resistor_SMD:R_0805_2012Metric_Pad1.20x1.40mm_HandSolder"
"R8","220k","Resistor_SMD:R_0805_2012Metric_Pad1.20x1.40mm_HandSolder"
"R9","47k","Resistor_SMD:R_0805_2012Metric_Pad1.20x1.40mm_HandSolder"
"R10","1M","Resistor_SMD:R_0805_2012Metric_Pad1.20x1.40mm_HandSolder"
"R12","470k","Resistor_SMD:R_0805_2012Metric_Pad1.20x1.40mm_HandSolder"
"R14","10k","Resistor_SMD:R_0805_2012Metric_Pad1.20x1.40mm_HandSolder"
"R15","100k","Resistor_SMD:R_0805_2012Metric_Pad1.20x1.40mm_HandSolder"
"R16","5k1","Resistor_SMD:R_0805_2012Metric_Pad1.20x1.40mm_HandSolder"
"R17","5k1","Resistor_SMD:R_0805_2012Metric_Pad1.20x1.40mm_HandSolder"
"R18","100k","Resistor_SMD:R_0805_2012Metric_Pad1.20x1.40mm_HandSolder"
"R19","100","Resistor_SMD:R_0805_2012Metric_Pad1.20x1.40mm_HandSolder"
"R20","1k","Resistor_SMD:R_0805_2012Metric_Pad1.20x1.40mm_HandSolder"
"R21","47k","Resistor_SMD:R_0805_2012Metric_Pad1.20x1.40mm_HandSolder"
"R22","47k","Resistor_SMD:R_0805_2012Metric_Pad1.20x1.40mm_HandSolder"
"R23","47k","Resistor_SMD:R_0805_2012Metric_Pad1.20x1.40mm_HandSolder"
"R24","47k","Resistor_SMD:R_0805_2012Metric_Pad1.20x1.40mm_HandSolder"
"R25","47k","Resistor_SMD:R_0805_2012Metric_Pad1.20x1.40mm_HandSolder"
"R26","470k","Resistor_SMD:R_0805_2012Metric_Pad1.20x1.40mm_HandSolder"
"R27","1M","Resistor_SMD:R_0805_2012Metric_Pad1.20x1.40mm_HandSolder"
"R28","2k2","Resistor_SMD:R_0805_2012Metric_Pad1.20x1.40mm_HandSolder"
"R29","2k2","Resistor_SMD:R_0805_2012Metric_Pad1.20x1.40mm_HandSolder"
"SW1","SW_Push","footprints:SW_Cherry_MX_1.00u_PCB"
"SW2","SW_Push","footprints:SW_Cherry_MX_1.00u_PCB"
"SW3","SW_Push","footprints:SW_Cherry_MX_1.00u_PCB"
"SW4","SW_Push","footprints:SW_Cherry_MX_1.00u_PCB"
"SW5","SW_Push","footprints:SW_Cherry_MX_1.00u_PCB"
"SW6","SW_Push","footprints:SW_Cherry_MX_1.00u_PCB"
"SW7","SW_Push","footprints:SW_Cherry_MX_1.00u_PCB"
"SW8","SW_Push","footprints:SW_Cherry_MX_1.00u_PCB"
"SW9","SW_Push","footprints:SW_Cherry_MX_1.00u_PCB"
"SW10","SW_Push","footprints:SW_Cherry_MX_1.00u_PCB"
"SW11","SW_Push","footprints:SW_Cherry_MX_1.00u_PCB"
"SW12","SW_Push","footprints:SW_Cherry_MX_1.00u_PCB"
"SW13","SW_Push","footprints:SW_Cherry_MX_1.00u_PCB"
"SW14","SW_Push","footprints:SW_Cherry_MX_1.00u_PCB"
"SW15","SW_Push","footprints:SW_Cherry_MX_1.00u_PCB"
"SW16","SW_Push","footprints:SW_Cherry_MX_1.00u_PCB"
"SW17","SW_Push","footprints:SW_Cherry_MX_1.00u_PCB"
"SW18","SW_Push","footprints:SW_Cherry_MX_1.00u_PCB"
"SW19","SW_Push","footprints:SW_Cherry_MX_1.00u_PCB"
"SW20","SW_Push","footprints:SW_Cherry_MX_1.00u_PCB"
"SW21","Encoder","footprints:RotaryEncoder_Alps_EC11E-Switch_Vertical_H20mm"
"SW22","SW_Push","Button_Switch_SMD:SW_SPST_PTS647_Sx38"
"U1","LTC4054","Package_TO_SOT_SMD:TSOT-23-5"
"U2","STI3411A","Package_TO_SOT_SMD:TSOT-23-5"
"U3","74HC595","Package_SO:TSSOP-16_4.4x5mm_P0.65mm"
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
